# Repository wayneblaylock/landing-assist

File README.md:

# landing-assist

Pilot-facing landing-assist advisory for experimental-aircraft flight test.

- `hardware/` — schematic, bill of materials
- `display/` — pilot horizon GUI (artificial horizon, pitch cues, height tape)
- `firmware/` — ESP-IDF project for firmware

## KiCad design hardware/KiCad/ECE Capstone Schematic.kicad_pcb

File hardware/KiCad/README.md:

ECE Capstone KiCad schematic and PCB design files

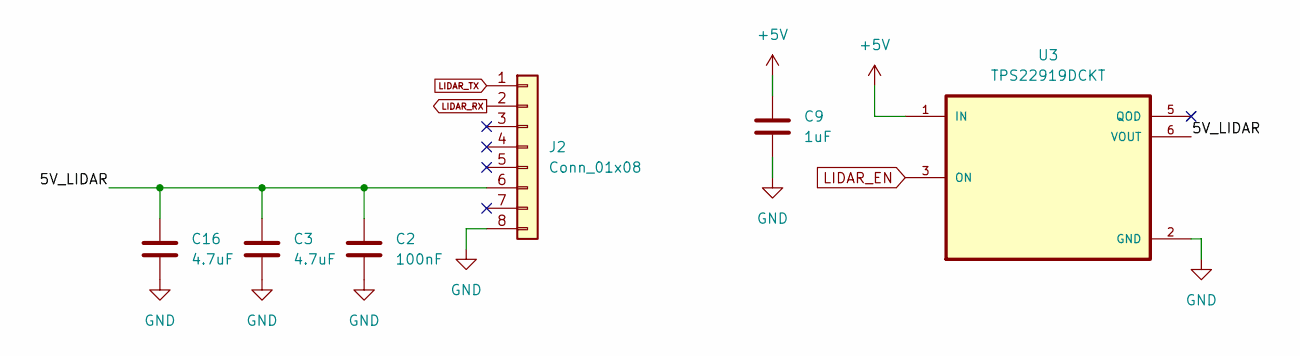
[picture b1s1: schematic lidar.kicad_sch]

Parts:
C2: 100nF; C_0201_0603Metric_Pad0.64x0.40mm_HandSolder
C3, C16: 4.7uF; C_0603_1608Metric_Pad1.08x0.95mm_HandSolder
C9: 1uF; C_0603_1608Metric_Pad1.08x0.95mm_HandSolder
J2: Conn_01x08; JST_SUR_SM08B-SURS-TF_1x08-1MP_P0.80mm_Horizontal
U3: TPS22919DCKT; SOT-363_SC-70-6; DigiKey_Part_Number 296-53421-1-ND

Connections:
+5V: C9.1, U3.1 (IN); also elsewhere on the board
/LiDAR/5V_LIDAR: C2.1, C3.1, C16.1, J2.6, U3.6 (VOUT)
GND: C2.2, C3.2, C9.2, C16.2, J2.8, U3.2 (GND); also elsewhere on the board
LIDAR_EN: U3.3 (ON); also elsewhere on the board
LIDAR_RX: J2.2; also elsewhere on the board
LIDAR_TX: J2.1; also elsewhere on the board

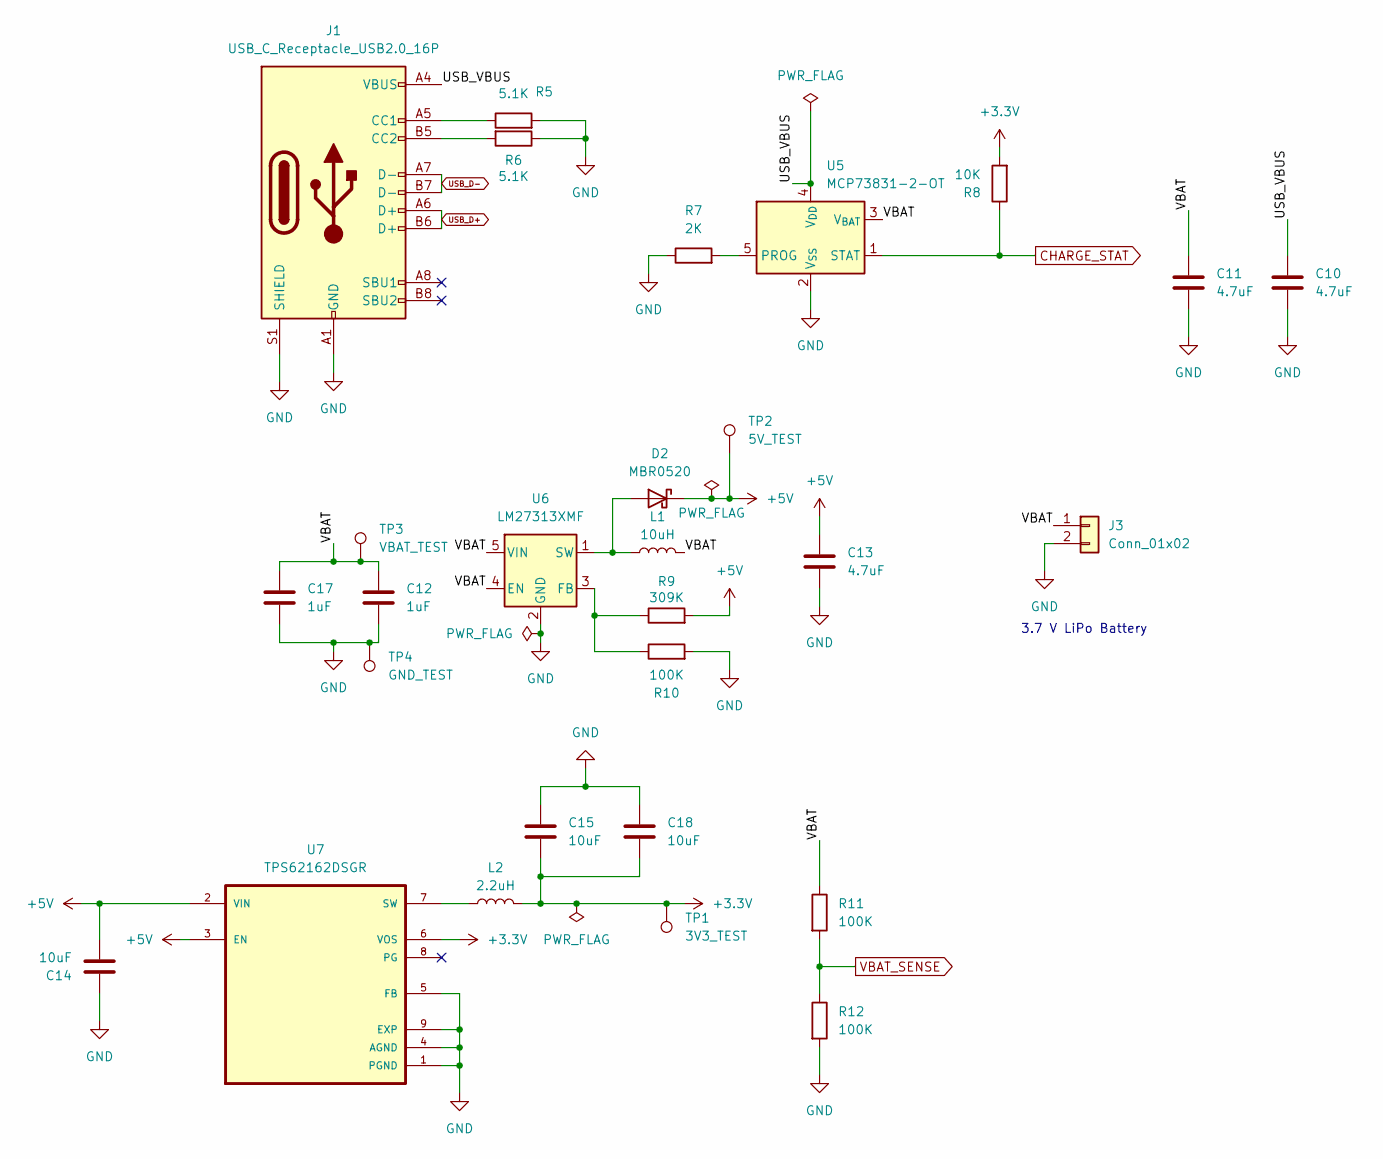
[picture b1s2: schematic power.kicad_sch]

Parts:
C10, C11, C13: 4.7uF; C_0603_1608Metric_Pad1.08x0.95mm_HandSolder
C12, C17: 1uF; C_0603_1608Metric_Pad1.08x0.95mm_HandSolder
C14: 10uF; C_0603_1608Metric_Pad1.08x0.95mm_HandSolder
C15, C18: 10uF; C_0805_2012Metric_Pad1.18x1.45mm_HandSolder
D2: MBR0520; D_SOD-123
J1: USB_C_Receptacle_USB2.0_16P; 10176546-00011LF_KiCad9
J3: Conn_01x02; JST_PH_S2B-PH-K_1x02_P2.00mm_Horizontal
L1: 10uH; L_TDK_VLS6045EX_VLS6045AF
L2: 2.2uH; IND_VLS252012ET-2R2M
R5, R6: 5.1K; R_0603_1608Metric_Pad0.98x0.95mm_HandSolder
R7: 2K; R_0603_1608Metric_Pad0.98x0.95mm_HandSolder
R8: 10K; R_0603_1608Metric_Pad0.98x0.95mm_HandSolder
R9: 309K; R_0603_1608Metric_Pad0.98x0.95mm_HandSolder
R10, R11, R12: 100K; R_0603_1608Metric_Pad0.98x0.95mm_HandSolder
TP1: 3V3_TEST; TestPoint_Pad_D1.5mm
TP2: 5V_TEST; TestPoint_Pad_D1.5mm
TP3: VBAT_TEST; TestPoint_Pad_D1.5mm
TP4: GND_TEST; TestPoint_Pad_D1.5mm
U5: MCP73831-2-OT; SOT-23-5
U6: LM27313XMF; SOT-23-5
U7: TPS62162DSGR; Texas_DSG0008A_WSON-8-1EP_2x2mm_P0.5mm_EP0.9x1.6mm; PARTREV E; DigiKey_Part_Number 296-43671-1-ND

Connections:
+3.3V: C15.2, C18.2, L2.2, R8.2, TP1.1, U7.6 (VOS); also elsewhere on the board
+5V: C13.1, C14.2, D2.1 (K), R9.2, TP2.1, U7.2 (VIN), U7.3 (EN); also elsewhere on the board
/POWER/USB_VBUS: C10.1, J1.A4 (VBUS), J1.A9 (VBUS), J1.B4 (VBUS), J1.B9 (VBUS), U5.4 (V_{DD})
/POWER/VBAT: C11.1, C12.1, C17.1, J3.1, L1.2, R11.1, TP3.1, U5.3 (V_{BAT}), U6.4 (EN), U6.5 (VIN)
CHARGE_STAT: R8.1, U5.1 (STAT); also elsewhere on the board
GND: C10.2, C11.2, C12.2, C13.2, C14.1, C15.1, C17.2, C18.1, J1.A1 (GND), J1.A12 (GND), J1.B1 (GND), J1.B12 (GND), J1.S1 (SHIELD), J3.2, R5.2, R6.1, R7.1, R10.2, R12.2, TP4.1, U5.2 (V_{SS}), U6.2 (GND), U7.1 (PGND), U7.4 (AGND), U7.5 (FB), U7.9 (EXP); also elsewhere on the board
unnamed: D2.2 (A), L1.1, U6.1 (SW)
unnamed: J1.A5 (CC1), R5.1
unnamed: J1.B5 (CC2), R6.2
unnamed: R7.2, U5.5 (PROG)
unnamed: R9.1, R10.1, U6.3 (FB)
unnamed: L2.1, U7.7 (SW)
USB_D+: J1.A6 (D+), J1.B6 (D+); also elsewhere on the board
USB_D-: J1.A7 (D-), J1.B7 (D-); also elsewhere on the board
VBAT_SENSE: R11.2, R12.1; also elsewhere on the board

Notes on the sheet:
3.7 V LiPo Battery

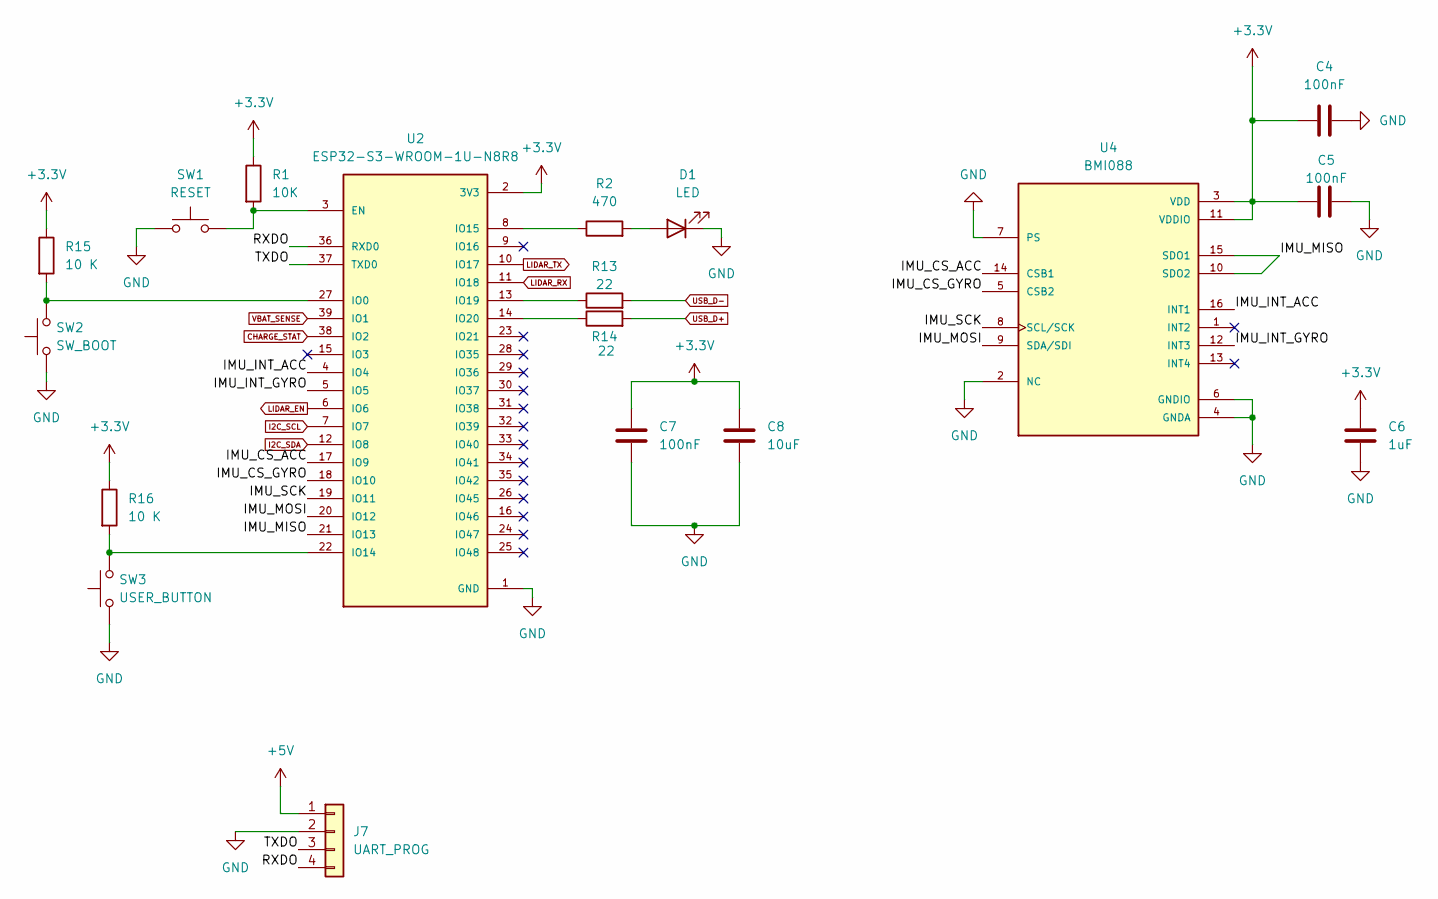
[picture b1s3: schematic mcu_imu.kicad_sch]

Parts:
C4, C5, C7: 100nF; C_0201_0603Metric_Pad0.64x0.40mm_HandSolder
C6: 1uF; C_0603_1608Metric_Pad1.08x0.95mm_HandSolder
C8: 10uF; C_0603_1608Metric_Pad1.08x0.95mm_HandSolder
D1: LED; LED_0603_1608Metric_Pad1.05x0.95mm_HandSolder
J7: UART_PROG; PinHeader_1x04_P2.54mm_Vertical
R1: 10K; R_0603_1608Metric_Pad0.98x0.95mm_HandSolder
R2: 470; R_0603_1608Metric_Pad0.98x0.95mm_HandSolder
R13, R14: 22; R_0402_1005Metric_Pad0.72x0.64mm_HandSolder
R15, R16: 10 K; R_0603_1608Metric_Pad0.98x0.95mm_HandSolder
SW1: RESET; SW_PUSH_6mm
SW2: SW_BOOT; SW_PUSH_6mm
SW3: USER_BUTTON; SW_PUSH_6mm
U2: ESP32-S3-WROOM-1U-N8R8; ESP32-S3-WROOM-1U; PARTREV v1.1; DigiKey_Part_Number 1965-ESP32-S3-WROOM-1U-N8R8CT-ND
U4: BMI088; Bosch_LGA-16_4.5x3mm_P0.5mm_LayoutBorder7x1y_ClockwisePinNu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; DigiKey_Part_Number 828-1082-1-ND

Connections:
+3.3V: C4.1, C5.1, C6.1, C7.1, C8.1, R1.1, R15.1, R16.1, U2.2 (3V3), U4.3 (VDD), U4.11 (VDDIO); also elsewhere on the board
+5V: J7.1; also elsewhere on the board
/MCU+IMU/IMU_CS_ACC: U2.17 (IO9), U4.14 (CSB1)
/MCU+IMU/IMU_CS_GYRO: U2.18 (IO10), U4.5 (CSB2)
/MCU+IMU/IMU_INT_ACC: U2.4 (IO4), U4.16 (INT1)
/MCU+IMU/IMU_INT_GYRO: U2.5 (IO5), U4.12 (INT3)
/MCU+IMU/IMU_MISO: U2.21 (IO13), U4.10 (SDO2), U4.15 (SDO1)
/MCU+IMU/IMU_MOSI: U2.20 (IO12), U4.9 (SDA/SDI)
/MCU+IMU/IMU_SCK: U2.19 (IO11), U4.8 (SCL/SCK)
/MCU+IMU/RXDO: J7.4, U2.36 (RXD0)
/MCU+IMU/TXDO: J7.3, U2.37 (TXD0)
CHARGE_STAT: U2.38 (IO2); also elsewhere on the board
GND: C4.2, C5.2, C6.2, C7.2, C8.2, D1.1 (K), J7.2, SW1.1, SW2.1, SW3.1, U2.1 (GND), U2.40 (GND), U2.41 (GND), U4.2 (NC), U4.4 (GNDA), U4.6 (GNDIO), U4.7 (PS); also elsewhere on the board
I2C_SCL: U2.7 (IO7); also elsewhere on the board
I2C_SDA: U2.12 (IO8); also elsewhere on the board
LIDAR_EN: U2.6 (IO6); also elsewhere on the board
LIDAR_RX: U2.11 (IO18); also elsewhere on the board
LIDAR_TX: U2.10 (IO17); also elsewhere on the board
unnamed: D1.2 (A), R2.2
unnamed: R1.2, SW1.2, U2.3 (EN)
unnamed: R15.2, SW2.2, U2.27 (IO0)
unnamed: R16.2, SW3.2, U2.22 (IO14)
unnamed: R2.1, U2.8 (IO15)
unnamed: R13.1, U2.13 (IO19)
unnamed: R14.1, U2.14 (IO20)
USB_D+: R14.2; also elsewhere on the board
USB_D-: R13.2; also elsewhere on the board
VBAT_SENSE: U2.39 (IO1); also elsewhere on the board

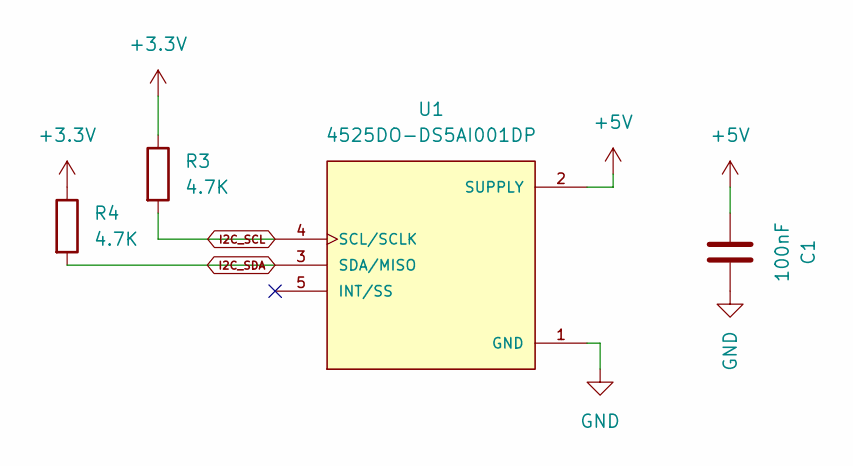
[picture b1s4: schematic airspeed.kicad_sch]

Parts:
C1: 100nF; C_0201_0603Metric_Pad0.64x0.40mm_HandSolder
R3, R4: 4.7K; R_0603_1608Metric_Pad0.98x0.95mm_HandSolder
U1: 4525DO-DS5AI001DP; TE_4525DO-DS5AI001DP; DigiKey_Part_Number 223-1110-ND

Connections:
+3.3V: R3.1, R4.1; also elsewhere on the board
+5V: C1.1, U1.2 (SUPPLY); also elsewhere on the board
GND: C1.2, U1.1 (GND); also elsewhere on the board
I2C_SCL: R3.2, U1.4 (SCL/SCLK); also elsewhere on the board
I2C_SDA: R4.2, U1.3 (SDA/MISO); also elsewhere on the board

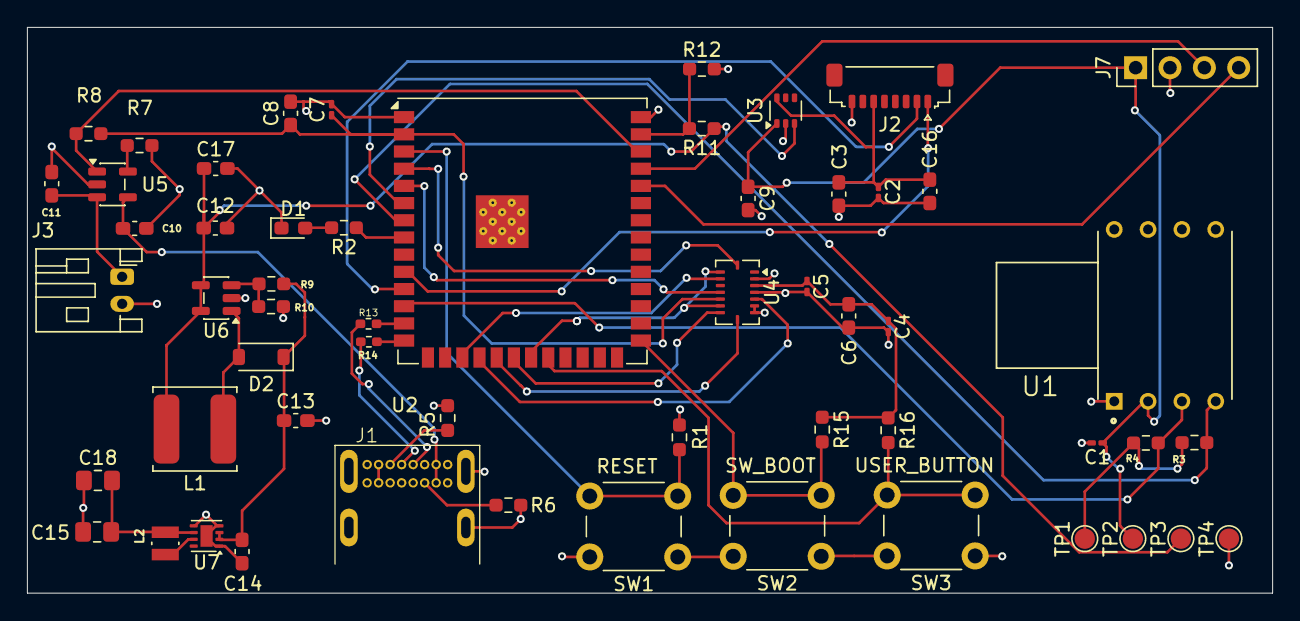
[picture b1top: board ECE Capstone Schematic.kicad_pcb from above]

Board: 4 copper layers, 92.0 x 41.8 mm, 56 parts (0 on the bottom side), 37 nets.
